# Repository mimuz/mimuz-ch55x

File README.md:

# mi:muz:ch55x Tiny USB MIDI Library for Ch55xduino

An Tiny library of USB MIDI for Deqing Sun's [Ch55xduino](https://github.com/DeqingSun/ch55xduino).

Support only 3 MIDI messages are :

- MIDI Note ON
- MIDI Note OFF
- MIDI Control Change

## Usage

### 1. Installing Arduino Software to your PC

Download and install the IDE for your environment from the URL below.

https://www.arduino.cc/en/software

### 2. Adding Ch55xduino to Arduino IDE

Add Deqing Sun's Ch55xduino to Arduino IDE by referring to the URL below.

https://github.com/DeqingSun/ch55xduino

### 3. Installing this library

Enter the following command in your terminal software to download this library.

```
cd <your arduino library path>
git clone git@github.com:mimuz/mimuz-ch55x.git
```

Please restart the Arduino IDE.

### 4. Programming your CH55x board

First select the your Board from `Tools > Board > CH55x Boards`.
For example, your board is a CH552 board, select `CH552 Board`.

Next, Select USB RAM Setting to `USER CODE w/ 148B USB ram` from `[Tools > USB Settings]`.

Uploading method is the same as the standard method of Ch55xduino.

Boards that have never been programmed with ch55xduino must be programmed with DFU. (Hold down the BOOT button and connect to USB)
After the second time, you can write via USB serial.

## APIs

### Initializer

#### `USBInit()`

Initialize the mi:muz functions. Call `USBInit()` on `setup()`.

### Event handler

#### `processMIDIMessage()`

This function is a event handler.    
When any MIDI event received, it call the callback functions.    
If your application set any callback functions to handle MIDI Event, `processMIDIMessage()` should place in `loop()`.    

### callback function registers

These callback function registers are set callback functions that called when MIDI message received.    
If you need to receive MIDI Message, be sure to call any function before `USBInit()` in `setup()`.    

#### `setHdlNoteOff(hdlNoteOff pfunc)`

Registers a callback function to be called when a `MIDI Note OFF` message is received.    
Make the Callback function to be set to parameter with the following prototype.

```
void onHandleNoteOff(__xdata uint8_t ch, __xdata uint8_t note);

- __xdata uint8_t ch : MIDI Channel
- __xdata uint8_t note : Note Number
```

#### `setHdlNoteOn(hdlMidiMessage pfunc)`

Registers a callback function to be called when a `MIDI Note ON` message is received.    
Make the Callback function to be set to parameter with the following prototype.

```
void onHandleNoteOn(__xdata uint8_t ch, __xdata uint8_t note, __xdata uint8_t vel);

- __xdata uint8_t ch : MIDI Channel
- __xdata uint8_t note : Note Number
- __xdata uint8_t vel : Velocity

```

#### `setHdlCtlChange(hdlMidiMessage pfunc)`

Registers a callback function to be called when a `MIDI Control Change` message is received.    
Make the Callback function to be set to parameter with the following prototype.

```
void onHandleControlChange(__xdata uint8_t ch, __xdata uint8_t num, __xdata uint8_t val);

- __xdata uint8_t ch : MIDI Channel
- __xdata uint8_t num : Control Number
- __xdata uint8_t val : Value

```

### MIDI Event senders

#### `sendNoteOn(uint8_t ch, uint8_t note, uint8_t vel)`

Send a MIDI Note On msessage.

#### `sendNoteOff(uint8_t ch, uint8_t note)`

Send a MIDI Note Off msessage.

#### `sendCtlChange(uint8_t ch, uint8_t num, uint8_t value)`

Send a MIDI Control Change msessage.

## Licenses

LGPL2.1

## About USB VID/Pid

Currently this library uses the PID issued from [pid.code](https://pid.codes) for [mimuz-can Lite](https://pid.codes/1209/DF02/). Because we are planning the next version of mimuz-can Lite as the first product using the library.    
It is not appropriate to use this PID for different products, so please change the VID/PID when using it.    

## for Simple Testing (examples/midi-callback)

Write [midi-callback](./examples/midi-callback), connect the ch55x board with LED connected to P30 to your PC with a USB cable, and open the following site with a Chrome browser.

- [testing site](https://mimuz.github.io/mimuz-ch55x/)    

The LED should blink at intervals of approximately 1 second.

## Reference Board Design (v1.0)

mimuz:ch55x supports various CH55x boards, We made a reference board design for mimuz-ch55x as an example.

### board preview

### schematics

### Autodesk EAGLE data

- [Autodesk Eagle Data (.sch .brd .lbr)](./board/eagle)

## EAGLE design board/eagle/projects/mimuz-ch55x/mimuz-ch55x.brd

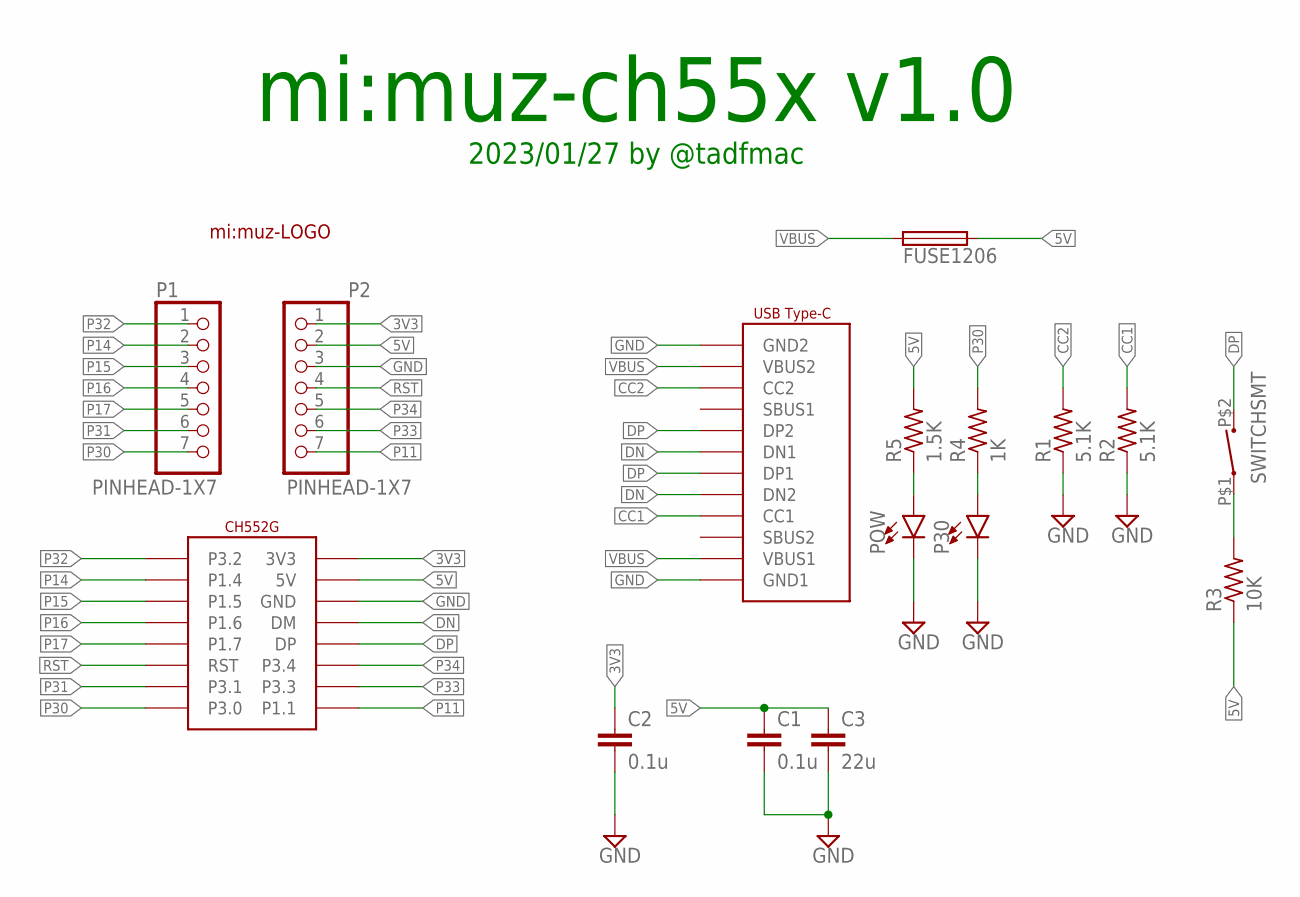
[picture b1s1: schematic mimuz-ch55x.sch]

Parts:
*: CH552G; SOIC16
C1, C2: 0.1u; C0603
C3: 22u; C0805
P1, P2: PINHEAD-1X7
P30: LED; LED-0603
POW: LED; LED-0603
R1, R2: 5.1K; R0603
R3: 10K; R0603
R4: 1K; R0603
R5: 1.5K; R0603
U$1: MIMUZ6MM; MIMUZ-SMALL
U$2: USB-C
U$3: FUSE1206; F1206
U$4: SWITCHSMT; SWITCH-SMT-2*4*3

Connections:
3V3: *.16 (3V3), C2.1, P2.1
5V: *.15 (5V), C1.1, C3.1, P2.2, R3.1, R5.2, U$3.2
CC1: R2.2, U$2.CC1
CC2: R1.2, U$2.CC2
DN: *.13 (DM), U$2.DN1, U$2.DN2
DP: *.12 (DP), U$2.DP1, U$2.DP2, U$4.P$2 (2)
GND: *.14 (GND), C1.2, C2.2, C3.2, P2.3, P30.C, POW.C, R1.1, R2.1, U$2.GND1, U$2.GND2
unnamed: R3.2, U$4.P$1 (1)
unnamed: POW.A, R5.1
unnamed: P30.A, R4.1
P11: *.9 (P1.1), P2.7
P14: *.2 (P1.4), P1.2
P15: *.3 (P1.5), P1.3
P16: *.4 (P1.6), P1.4
P17: *.5 (P1.7), P1.5
P30: *.8 (P3.0), P1.7, R4.2
P31: *.7 (P3.1), P1.6
P32: *.1 (P3.2), P1.1
P33: *.10 (P3.3), P2.6
P34: *.11 (P3.4), P2.5
RST: *.6 (RST), P2.4
VBUS: U$2.VBUS1, U$2.VBUS2, U$3.1

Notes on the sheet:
mi:muz-ch55x v1.0
2023/01/27 by @tadfmac

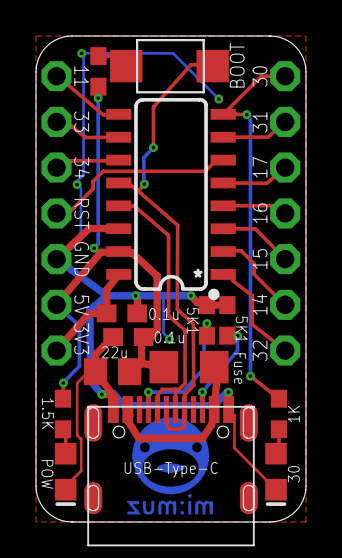
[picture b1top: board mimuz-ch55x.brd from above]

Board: 2 copper layers, 15.0 x 27.0 mm, 17 parts (1 on the bottom side), 22 nets.

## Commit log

2023-01-14 fix typo
2023-01-14 change name in library.properties
2023-01-14 change version -> 0.1.1
2023-01-21 add reference board design
2023-01-23 add board-view src file
2023-01-26 mod mimuz-ch55x.brd
2023-01-26 fix name
2023-03-10 add CC numbers as enum
2023-03-10 add sendNRPN
2023-03-10 add sendPitchbend
2023-08-12 #5 fix device startion failed on win10, #1 change USB PID
2023-08-12 fix #4
2024-02-28 Update mimuz-ch55x.c
    "I suspect there have been recent changes in the CH55xDuino core that might have caused the library to fail to compile. By making this adjustment in the file, the library is operational once more."
